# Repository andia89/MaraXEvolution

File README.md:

# MaraX Evolution - Main Controller

### Screenshot

### Videos
|  |  |
|:--:| :--:| 
| *Pressure profiling with a blind flange. The pressure follows a complicated profile* | *Real shot with the custom Controller. The profile is set to produce a flat 9bar shot that stops at 40g (since the valve is not closed by the lever there will always be some additional coffee coming out after the pump stopped). As one can see the pressure neatly follows the 9bar (at one point I adjusted with the flow control paddle so that is when the pressure dropped). The grind was way to fine for this shot :D* |

This repository contains the hardware design and firmware for the **MaraX Evolution** main controller board. This project is designed to replace the stock controller of the Lelit Mara X espresso machine, adding advanced features such as PID temperature control, pressure profiling, weighing scale integration, and WiFi connectivity.

## Features

### Core Control
* **Hybrid Thermal Control:** Utilizes a custom **Feed-Forward + PID algorithm** (`feedForwardHeater`) that estimates heat loss based on ambient vs. boiler temperature, offering better stability than standard PIDs.
* **Dual-PID Architecture:** Dedicated PID loops for Temperature (Boiler/HX) and Pump (Pressure/Flow).
* **Smart State Machine:** Manages states including `COOLING_FLUSH`, `STEAM_BOOST`, and `STANDBY`.
* Performs all tasks the original Lelit MaraX machine does as well (boiler refill, water tank presence detection, relay activations etc...)

### Profiling & Extraction
* **Pressure Profiling:** Real-time pump dimmer control via Zero-Cross detection.
* **Flow Profiling:** (Requires [MaraX Evolution Scale](https://github.com/andia89/MaraXEvolution-Scale/)) Target specific flow rates (g/s) using Kalman-filtered weight data.
* **Gravimetric stopping:** (Requires [MaraX Evolution Scale](https://github.com/andia89/MaraXEvolution-Scale/)) Stop the shot after a set amount of time or when a certain weight is reached
* **Advanced Profiles:** Supports manual control, flat 9-bar shots, or complex JSON-based profiles (Ramped or Stepped).

### Integration & Connectivity
* **WiFi & MQTT:** Full smart home integration. Reports sensors (`boiler_temp`, `pressure`, `weight`) and accepts commands remotely.
* **Telnet CLI:** Built-in command-line interface for debugging and calibration over WiFi.
* **ESP-NOW HMI:** Low-latency connection to the optional [MaraX Evolution HMI](https://github.com/andia89/maraxevolution-hmi).
* **OTA Updates:** Update firmware wirelessly without opening the machine.

### Maintenance
* **Automated Cleaning:** Built-in backflush program (`CLEANING_START` -> `CLEANING_PUMPING` -> `PAUSE`).
* **Scale Calibration:** Integrated wizard for taring and calibrating the load cell.

## Repository Structure

* `controller_board/`: KiCad v6 hardware design files (schematics, PCB layout, and fabrication files).
* `firmware/`: PlatformIO project source code for the ESP32-based controller.

## Hardware Assembly

1.  **PCB Fabrication:** Use the Gerber and Drill files provided in `controller_board/jlcpcb/production_files/` to order the PCB.
2.  **Assembly:** Solder the components according to the BOM (`BOM-controller_board.csv`). The board features an Arduino-Nano ESP32 compatible footprint. See [Assembly](ASSEMBLY.md) for details
3.  **Installation:** Replace the existing Mara X controller with this board, ensuring all connections (sensors, pump, heating element) are mapped correctly.

## Firmware Compilation

The firmware is modular. You can enable/disable hardware features via `platformio.ini` build flags:

```cpp
build_flags = 
    -D HAS_PRESSURE_GAUGE
    -D HAS_SCALE
    -D HAS_SCREEN
```

The firmware is built using **PlatformIO**.

1.  Install [VSCode](https://code.visualstudio.com/) and the [PlatformIO extension](https://platformio.org/).
2.  Clone this repository.
3.  Open the `firmware` folder in PlatformIO.
4.  Configure `platformio.ini` if necessary (e.g., to select specific build environments or upload ports)
5.  Click the **Build** icon (checkmark) to compile.
6.  Connect your Arduino Nano ESP32 board via USB and click **Upload** (select `env:firmware` build environment).
7.  For subsequent uploads OTA should be enabled (you might have to adjust IP-address in `platformio.ini`) and selecting the `env:firmware-ota` environment

## [User Guide](USERGUIDE.md)

## [Parts list](PARTS.md)

## [Assembly instructions](ASSEMBLY.md)

## Support me

I had way too much fun building the MaraX Evolution—it turned into quite the obsession! I am definitely planning to tackle another coffee machine and give it the same "Evolution" treatment.

**However, espresso machines are expensive! :D**

If you enjoy this project or use it daily, please consider supporting me.

**Your Support = Your Vote**

When you support me on Ko-fi or Patreon, **please leave a comment telling me which coffee machine you want me to do next.**

Think of it as a voting system: As soon as I have enough funds to cover the machine with the most votes (and the parts to mod it), I will buy it, reverse-engineer it, and build an open-source controller for it. If you have the MaraX and still want to support me, you can also tell me if there is a specific feature you want to have!

I will keep track of the money earned and will update occasionally the votes on the different coffee machines that are requested

## Limitations
* The MaraX is a very good heatexchanger machine, using quite sophisticated hardware to achieve superior temperature stability than a lot of other HX machines out of the box. It is, however, not a dual boiler machine and as such perfect temperature control is almost impossible. I played around a lot with PID values and was able to come up with some good values (and some pretty sophisticated feed forward control), but still perfect stability is almost impossible (or only if one tunes the PID super conservative, but then it takes hours to heat the machine)
* This is not a cheap project. Most parts can be sourced pretty cheaply, but I used good ADC chips (the ADS1115) and one unfortunately obsolete LM1830 chip for boiler water level detection as well as a pretty expensive power supply for the 12V power. Most of these things could certainly be done cheaper (and maybe someday will). All in all expect to spend a bit of money if you go for the full set (which is recommended).
* In the end the softweare got waaaaay more complicated than I originally anticipated. Some software was written using AI but I went through all of it and made sure it made sense to me. There certainly will be bugs as there is an infinite amount of edge cases I certainly have not considered. Please report any bugs you may find

## Disclaimer & Safety Warning

**PLEASE READ CAREFULLY BEFORE PROCEEDING.**

**1. I am a Hobbyist, Not a Professional**
I am **not** a professional mechanical, electrical, or software engineer. This project was created purely as a personal hobby undertaking for educational purposes. The code and hardware designs provided here are **not** certified, tested to industrial standards, or guaranteed to be bug-free.

**2. Warranty Voiding**
Modifying your espresso machine, uploading custom firmware, or opening the chassis **will almost certainly void your manufacturer’s warranty**. By proceeding with any instructions or files from this repository, you accept full responsibility for the loss of any existing warranty or support from the original manufacturer.

**3. No Liability**
This software and hardware documentation is provided **"AS IS", WITHOUT WARRANTY OF ANY KIND**, express or implied.
* **I am not responsible** for any damage to your machine (bricking the device, burning out components, leaks, etc.).
* **I am not responsible** for any personal injury or property damage (including fire or electrical shock) resulting from the use of this project.
* **You assume all risk** associated with modifying your hardware and running this software.

**4. High Voltage & Pressure Warning**
Espresso machines involve **Mains Electricity (110V/220V)**, **Water**, and **High Pressure**. This is a dangerous combination.
* Never work on the machine while it is plugged in.
* Ensure you have a proper understanding of electrical safety before attempting any hardware modifications.
* Improper handling of the boiler or pressure lines can result in explosion or severe burns.

**Use this project entirely at your own risk.**

If you find anything that you think could be improved (be it software/electrical or mechanical side) please let me know, and feel free to open a Pull request

## Licensing
This project is dual-licensed to protect the work while allowing for personal study and modification.

* **Firmware:** The main source code located in the `/firmware` directory is licensed under the **PolyForm Noncommercial License 1.0.0**. You may modify and use it for personal projects, but you cannot use it for commercial products.
    * *Third-Party Libraries:* This firmware includes modified versions of the following libraries, which remain under their original licenses:
        * [dimmable-light](https://github.com/fabianoriccardi/dimmable-light): Licensed under **LGPL-2.1**.
        * [PID_v1](https://github.com/br3ttb/Arduino-PID-Library/tree/master): Licensed under **MIT License**.
        * [Simple Kalman Filter](https://github.com/denyssene/SimpleKalmanFilter): Licensed under **MIT License**.

* **Firmware:** The hardware designs, schematics, and 3D models located in the /controller_board and /hv_board directories are licensed under the Creative Commons Attribution-NonCommercial 4.0 International (CC BY-NC 4.0) license.

Please see the LICENSE file in each respective subdirectory for the full legal text.

## Similar projects
Idea for controlling the pump via an AC dimmer has been done in https://github.com/larszi/marax-pressure-mod. A complete overhaul of control software is currently proposed by the great project in https://github.com/variegated-coffee (they try to make a one-fit all solution though)

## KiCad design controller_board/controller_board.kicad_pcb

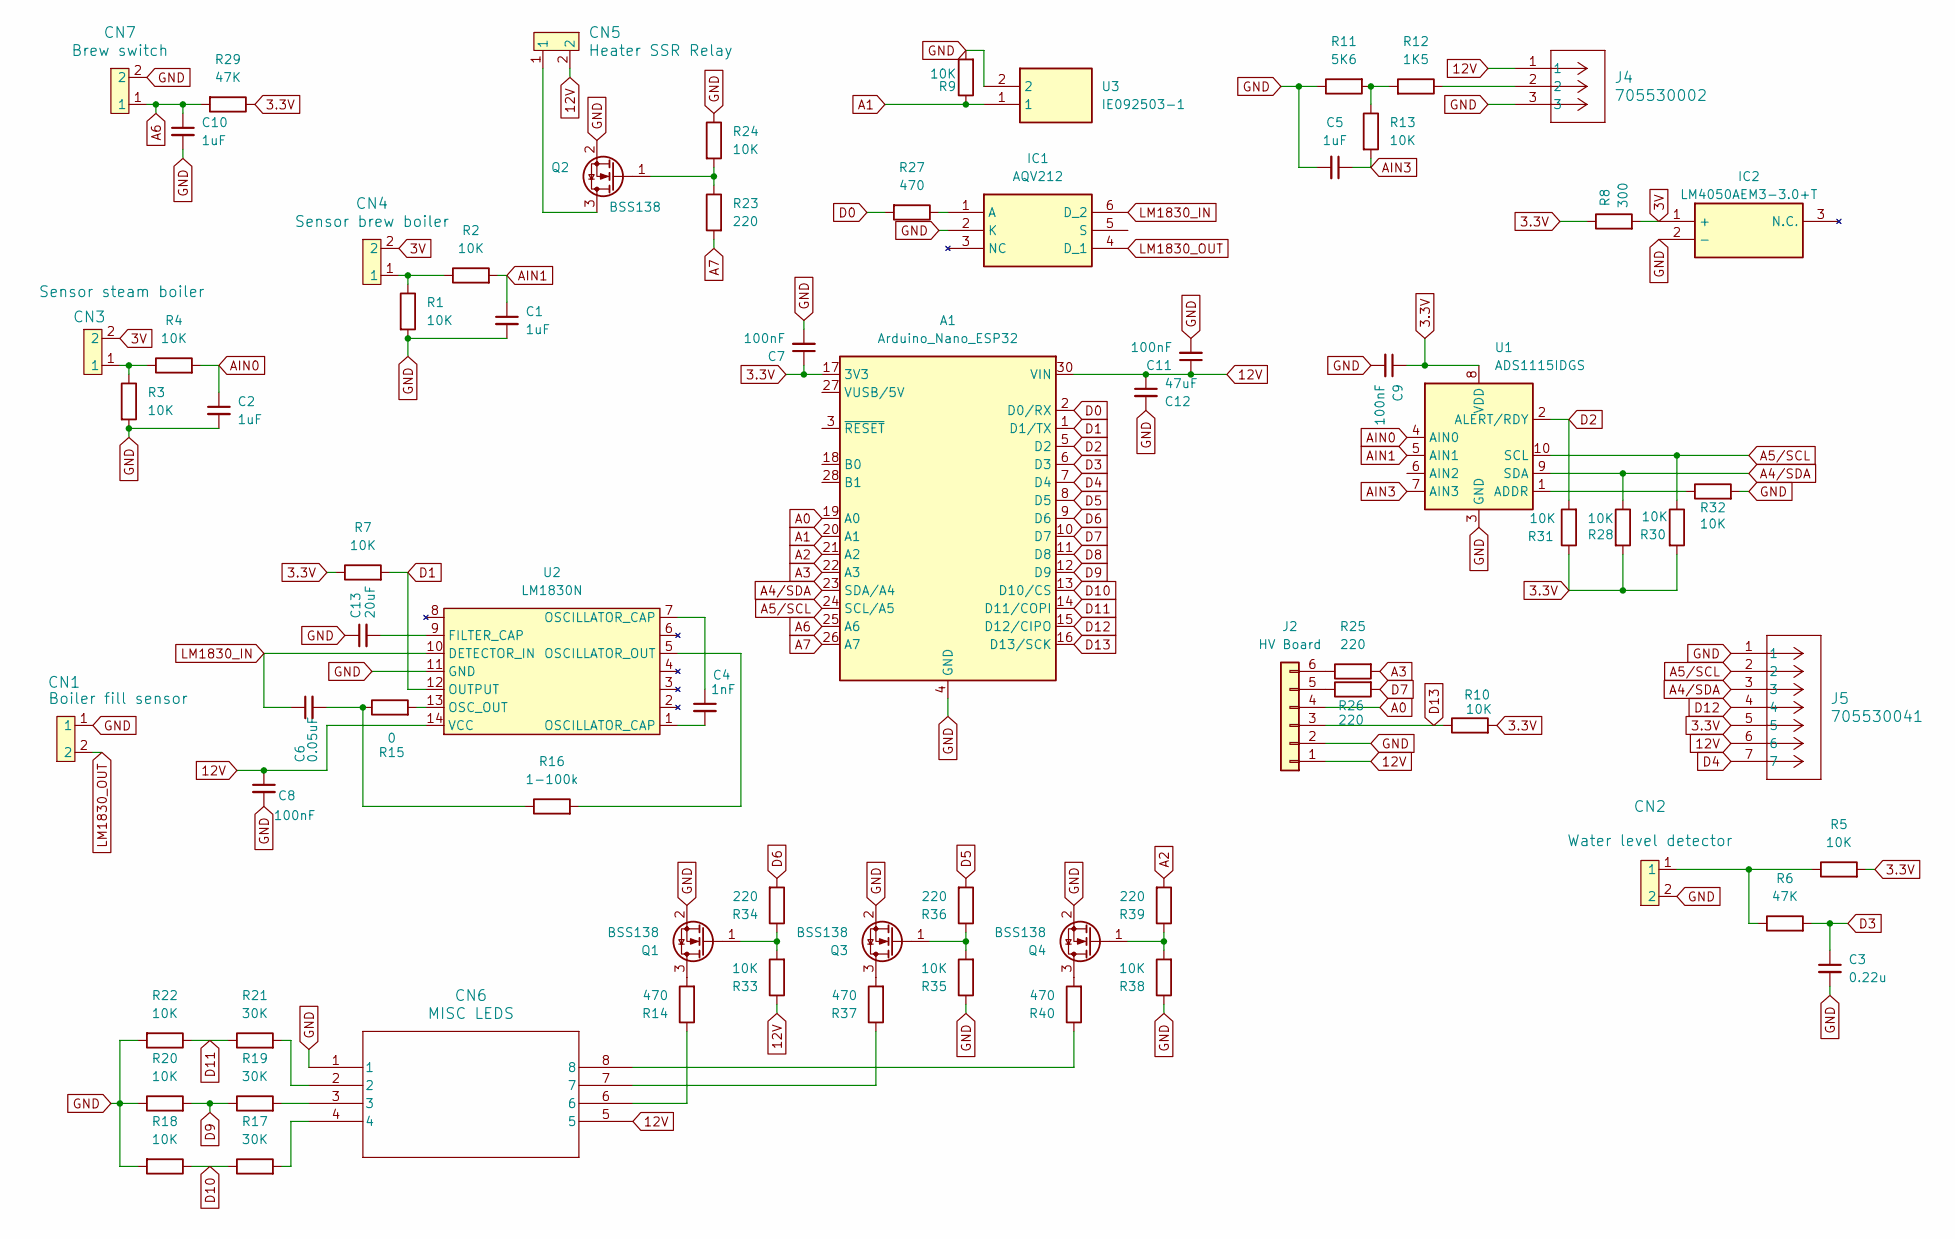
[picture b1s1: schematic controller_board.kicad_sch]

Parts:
A1: Arduino_Nano_ESP32; Arduino_Nano
C1, C2, C5, C10: 1uF; C_0805_2012Metric_Pad1.18x1.45mm_HandSolder
C3: 0.22u; C_0805_2012Metric_Pad1.18x1.45mm_HandSolder
C4: 1nF; C_0805_2012Metric_Pad1.18x1.45mm_HandSolder
C6: 0.05uF; C_0805_2012Metric_Pad1.18x1.45mm_HandSolder
C7, C8, C9, C11: 100nF; C_0805_2012Metric_Pad1.18x1.45mm_HandSolder
C12: 47uF; C_0805_2012Metric_Pad1.18x1.45mm_HandSolder
C13: 20uF; C_0805_2012Metric_Pad1.18x1.45mm_HandSolder
CN1: Boiler fill sensor; 280377-2_TYC
CN2: Water level detector; 280377-2_TYC
CN3: Sensor steam boiler; 280377-2_TYC
CN4: Sensor brew boiler; 280377-2_TYC
CN5: Heater SSR Relay; 280377-2_TYC
CN6: MISC LEDS; 280389-2_TYC
CN7: Brew switch; 280377-2_TYC
IC1: AQV212; DIP762W47P254L880H410Q6N; Mouser Part Number 769-AQV212
IC2: LM4050AEM3-3.0+T; SOT95P237X112-3N; Mouser Part Number 700-LM4050AEM3-3.0T
J2: HV Board; PinHeader_1x06_P2.00mm_Vertical
J4: 705530002; CONN_705530002_03_MOL
J5: 705530041; CONN_70553-xxxx_07_MOL
Q1, Q2, Q3, Q4: BSS138; SOT-23
R1, R2, R3, R4, R5, R7, R9, R10, R13, R18, R20, R22, R24, R28, R30, R31, R32, R33, R35, R38: 10K; R_0805_2012Metric_Pad1.20x1.40mm_HandSolder
R6, R29: 47K; R_0805_2012Metric_Pad1.20x1.40mm_HandSolder
R8: 300; R_0805_2012Metric_Pad1.20x1.40mm_HandSolder
R11: 5K6; R_0805_2012Metric_Pad1.20x1.40mm_HandSolder
R12: 1K5; R_0805_2012Metric_Pad1.20x1.40mm_HandSolder
R14, R27, R37, R40: 470; R_0805_2012Metric_Pad1.20x1.40mm_HandSolder
R15: 0; R_0805_2012Metric_Pad1.20x1.40mm_HandSolder
R16: 1-100k; R_0805_2012Metric_Pad1.20x1.40mm_HandSolder
R17, R19, R21: 30K; R_0805_2012Metric_Pad1.20x1.40mm_HandSolder
R23, R25, R26, R34, R36, R39: 220; R_0805_2012Metric_Pad1.20x1.40mm_HandSolder
U1: ADS1115IDGS; VSSOP-10_3x3mm_P0.5mm
U2: LM1830N; PDIP14_19P56X6P35_ONS
U3: IE092503-1; IE0925031; Mouser Part Number 497-IE092503-1

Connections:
3.3V: A1.17 (3V3), C7.1, C9.1, J5.5, R5.2, R7.1, R8.1, R10.2, R28.2, R29.1, R30.2, R31.1, U1.8 (VDD)
3V: CN3.2, CN4.2, IC2.1 (+), R8.2
12V: A1.30 (VIN), C8.1, C11.1, C12.1, CN5.2, CN6.5, J2.1, J4.1, J5.6, R33.1, U2.14 (VCC)
A0: A1.19 (A0), J2.4
A1: A1.20 (A1), R9.1, U3.1
A2: A1.21 (A2), R39.2
A3: A1.22 (A3), R25.2
A4/SDA: A1.23 (SDA/A4), J5.3, R28.1, U1.9 (SDA)
A5/SCL: A1.24 (SCL/A5), J5.2, R30.1, U1.10 (SCL)
A6: A1.25 (A6), C10.1, CN7.1, R29.2
A7: A1.26 (A7), R23.2
AIN0: C2.1, R4.2, U1.4 (AIN0)
AIN1: C1.1, R2.2, U1.5 (AIN1)
AIN3: C5.1, R13.2, U1.7 (AIN3)
D0: A1.2 (D0/RX), R27.2
D1: A1.1 (D1/TX), R7.2, U2.12 (OUTPUT)
D2: A1.5 (D2), R31.2, U1.2 (ALERT/RDY)
D3: A1.6 (D3), C3.1, R6.2
D4: A1.7 (D4), J5.7
D5: A1.8 (D5), R36.2
D6: A1.9 (D6), R34.2
D7: A1.10 (D7), R26.2
D8: A1.11 (D8)
D9: A1.12 (D9), R19.1, R20.2
D10: A1.13 (D10/CS), R17.1, R18.1
D11: A1.14 (D11/COPI), R21.1, R22.1
D12: A1.15 (D12/CIPO), J5.4
D13: A1.16 (D13/SCK), J2.3, R10.1
GND: A1.4 (GND), A1.29 (GND), C1.2, C2.2, C3.2, C5.2, C7.2, C8.2, C9.2, C10.2, C11.2, C12.2, C13.1, CN1.1, CN2.2, CN6.1, CN7.2, IC1.2 (K), IC2.2 (-), J2.2, J4.3, J5.1, Q1.2 (S), Q2.2 (S), Q3.2 (S), Q4.2 (S), R1.2, R3.2, R9.2, R11.1, R18.2, R20.1, R22.2, R24.1, R32.2, R35.1, R38.1, U1.3 (GND), U2.11 (GND), U3.2
LM1830_IN: C6.1, IC1.6 (D_2), U2.10 (DETECTOR_IN)
LM1830_OUT: CN1.2, IC1.4 (D_1)
unnamed: C4.1, U2.7 (OSCILLATOR_CAP)
unnamed: C4.2, U2.1 (OSCILLATOR_CAP)
unnamed: C6.2, R15.1, R16.1
unnamed: CN2.1, R5.1, R6.1
unnamed: CN3.1, R3.1, R4.1
unnamed: CN4.1, R1.1, R2.1
unnamed: CN6.2, R21.2
unnamed: CN6.3, R19.2
unnamed: CN6.4, R17.2
unnamed: CN6.6, R14.1
unnamed: CN6.7, R37.1
unnamed: CN6.8, R40.1
unnamed: IC1.1 (A), R27.1
unnamed: J2.5, R26.1
unnamed: J2.6, R25.1
unnamed: J4.2, R12.1
unnamed: Q1.3 (D), R14.2
unnamed: Q1.1 (G), R33.2, R34.1
unnamed: CN5.1, Q2.3 (D)
unnamed: Q2.1 (G), R23.1, R24.2
unnamed: Q3.3 (D), R37.2
unnamed: Q3.1 (G), R35.2, R36.1
unnamed: Q4.3 (D), R40.2
unnamed: Q4.1 (G), R38.2, R39.1
unnamed: R11.2, R12.2, R13.1
unnamed: R32.1, U1.1 (ADDR)
unnamed: C13.2, U2.9 (FILTER_CAP)
unnamed: R16.2, U2.5 (OSCILLATOR_OUT)
unnamed: R15.2, U2.13 (OSC_OUT)

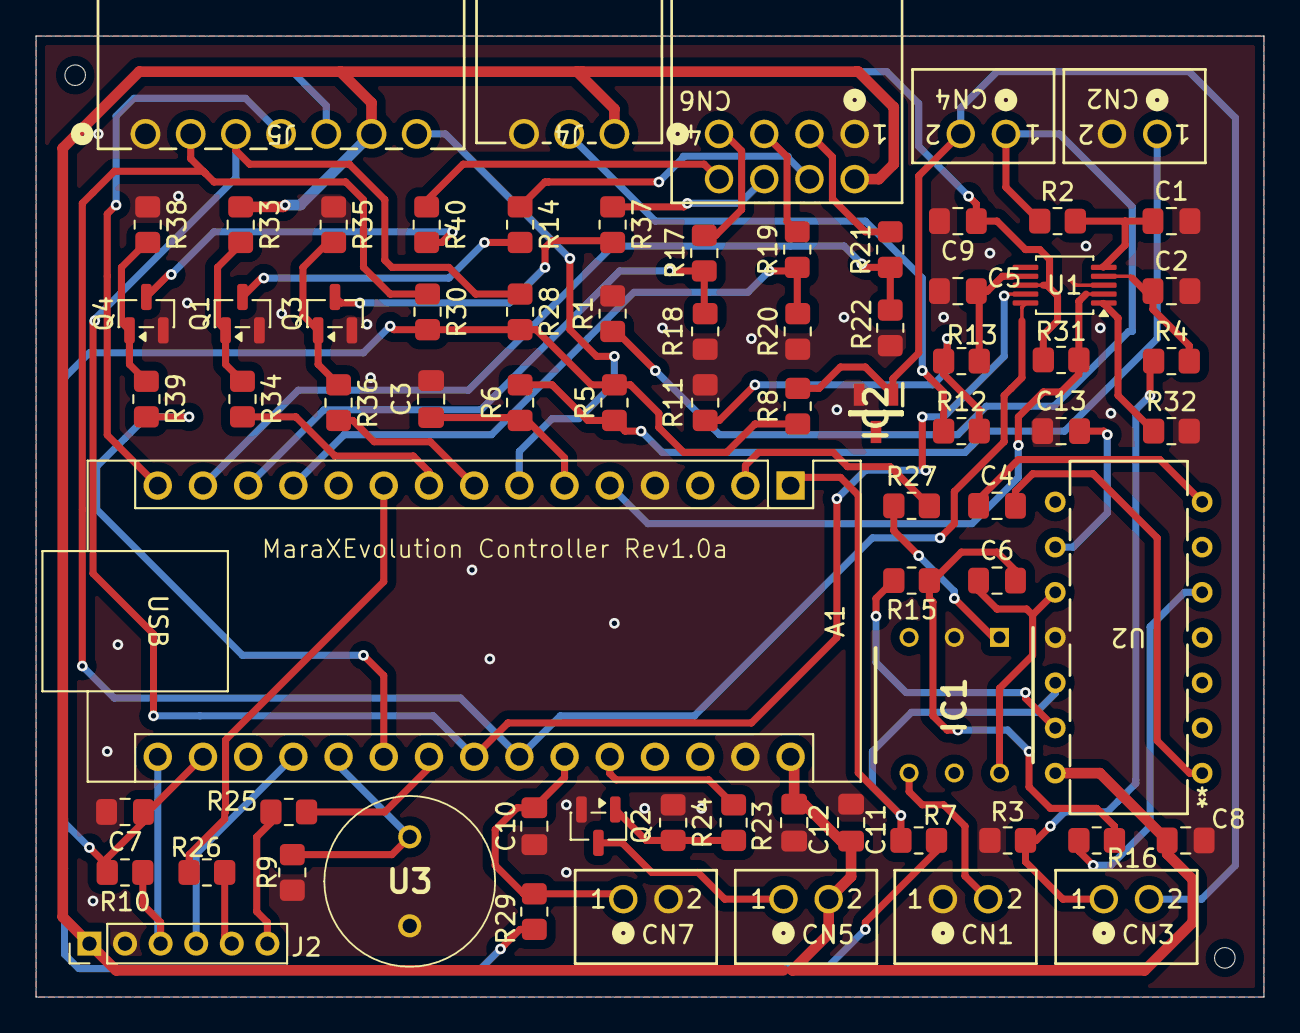
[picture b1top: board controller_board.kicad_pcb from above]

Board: 2 copper layers, 69.0 x 54.0 mm, 73 parts (0 on the bottom side), 59 nets.

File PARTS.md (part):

## Parts List

 * PCBs for both the controller board and the HV board. I had good experience with JLCPCB but PCBWay is also fine. The gerber files can be found in production_files in the jlcpcb folder. 

* Electronic parts for assembly. They are listed at the end of this section in [Controller board](#conroller-board) and [HV board](#hv-board)

* If you want to use a pressure transducer (this is necessary to do profiling based on pressure, and to electronically monitor the pressure). 
    * The board is designed for [this one](https://aliexpress.com/item/4000756631924.html?spm=a2g0o.ord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; specifically 0-1.6MPa at 0.5V-4.5V and a supply voltage of 12V
    * [T-Piece for pipe](https://www.landefeld.de/artikel/de/t-steckanschluss-5mm-5mm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 It is important to note that the MaraX uses 5mm pipes which are quite non-standard
    * [Pipe push fitting](https://www.landefeld.de/artikel/de/steckanschluss-m-innenge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
    * [5mm polyurethane pipe](https://www.landefeld.de/artikel/de/polyurethan-schlauch-5-x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; get 1m to have a bit left-over
    * [Molex connector](https://www.mouser.at/ProductDetail/Molex/50-57-9403?qs=u6Gr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 that has its mate on the controller board, with at least [3 Receptables that need to be crimped on the wire](https://www.mouser.at/ProductDetail/Molex/16-02-0102?qs=UAyr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
* If you want to use AC dimmer for flow/pressure profiling (and you either have the Pressure transducer and/or the scale installed) one additional (ideally heat-resistant cable) is necessary. Two [Connectors](https://www.mouser.at/ProductDetail/571-606501) like this one have to be crimped on a sufficiently long cable. 

### Controller Board

The BOM for the controller board is divided into **SMD components** (suitable for JLCPCB's SMT service) and **Handsolder components** (precision parts, connectors, and the microcontroller to be sourced from Mouser/DigiKey).

#### 1. SMD Components (JLCPCB SMT Service)
These components have LCSC part numbers included in the BOM and can be assembled by the JLCPCB SMT service. Alternatively they can be of course hand soldered. These Resistors and Capacitors are mainly used for Pull-up/down, current limiting and filtering, as such their exact values are not that important. The transistors are mainly used for switching LEDs. In both controller_board and hv_board folder there is a jlcpcb folder that contains all the necessary files for fabrication as well as SMT assembly.

| Comment | Designator | Footprint | LCSC Part | Qty |
| :--- | :--- | :--- | :--- | :--- |
| **0** | R15 | R 0805 | [C17477](https://lcsc.com/product-detail/C17477.html) | 1 |
| **0.05uF** | C6 | C 0805 | [C53134](https://lcsc.com/product-detail/C53134.html) | 1 |
| **0.22u** | C3 | C 0805 | [C5378](https://lcsc.com/product-detail/C5378.html) | 1 |
| **100nF** | C7, C8, C9, C11 | C 0805 | [C28233](https://lcsc.com/product-detail/C28233.html) | 4 |
| **1nF** | C4 | C 0805 | [C46653](https://lcsc.com/product-detail/C46653.html) | 1 |
| **1uF** | C1, C2, C5, C10 | C 0805 | [C28323](https://lcsc.com/product-detail/C28323.html) | 4 |
| **10K** | R1, R3, R5, R7, R9, R10, **R13**, R18, R20, R22, R24, R28, R30, R31, R32, R33, R35, R38 | R 0805 | [C17414](https://lcsc.com/product-detail/C17414.html) | 18 |
| **20uF** | C13 | C 0805 | [C45783](https://lcsc.com/product-detail/C45783.html) | 1 |
| **47uF** | C12 | C 0805 | [C28323](https://lcsc.com/product-detail/C28323.html) | 1 |
| **220** | R23, R25, R26, R34, R36, R39 | R 0805 | [C17557](https://lcsc.com/product-detail/C17557.html) | 6 |
| **300** | R8 | R 0805 | [C17617](https://lcsc.com/product-detail/C17617.html) | 1 |
| **30K** | R17, R19, R21 | R 0805 | [C17621](https://lcsc.com/product-detail/C17621.html) | 3 |
| **470** | R14, R27, R37, R40 | R 0805 | [C17710](https://lcsc.com/product-detail/C17710.html) | 4 |
| **47K** | R6, R29 | R 0805 | [C17713](https://lcsc.com/product-detail/C17713.html) | 2 |
| **BSS138** | Q1, Q2, Q3, Q4, Q5, Q6 | SOT-23 | [C15277](https://lcsc.com/product-detail/C15277.html) | 6 |

#### 2. Handsolder Components (Mouser / DigiKey)
These parts are not included in the SMT assembly and must be purchased separately.

**Precision Resistors**
*0.1% tolerance is recommended for these voltage dividers. If this is really necessary I am not sure, but I used 0.1% tolerance ones and it works great*

| Value | Designator | Qty | Link (Mouser) |
| :--- | :--- | :--- | :--- |
| **1K5** | R12 | 1 | [0805 1.5K 0.1%](https://www.mouser.com/c/?q=0805%20resistor%201.5kOhms%200.1%25) |
| **5K6** | R11 | 1 | [0805 5.6K 0.1%](https://www.mouser.com/c/?q=0805%20resistor%205.6kOhms%200.1%25) |
| **10K** | R2, R4 | 2 | [0805 10K 0.1%](https://www.mouser.com/c/?q=0805%20resistor%2010kOhms%200.1%25) |
| **-** | **R16** | **0** | **DNP (Do Not Populate)** |

**ICs & Modules**

| Part Name | Designator | Description | Qty | Link (Mouser) | Comment | 
| :--- | :--- | :--- | :--- | :--- | :--- |
| **Arduino Nano ESP32**| A1 | Microcontroller | 1 | [Arduino Nano ESP32](https://www.mouser.com/c/?q=Arduino%20Nano%20ESP32) | with headers if directly soldered to the board. Otherwise [Mill-Max](https://www.mill-max.com/products/new/precision-machined-pin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 headers are a way to socket it (there is not enough vertical space for standard machine headers)
| **ADS1115IDGS** | U1 | 16-Bit ADC | 1 | [ADS1115IDGS](https://www.mouser.com/c/?q=ADS1115IDGS) | Any ADS1115 will work fine
| **AQV212** | IC1 | PhotoMOS Relay | 1 | [AQV212](https://www.mouser.com/c/?q=AQV212%20DIP-6) | can be socketed using standard DIP-6 socket
| **IE092503-1** | U3 | Buzzer | 1 | [IE092503-1](https://www.mouser.com/c/?q=IE092503-1) | If you don't want a buzzer, can be omitted
| **LM4050AEM3-3.0** | IC2 | Voltage Reference 3.0V | 1 | [LM4050AEM3-3.0](https://www.mouser.com/c/?q=LM4050AEM3-3.0) | A precise voltage reference for temperature measurements

**Connectors**

| Part Name | Designator | Description | Qty | Link (Mouser) | Comment | 
| :--- | :--- | :--- | :--- | :--- | :--- |
| **280377-2** | CN1, CN2, CN3, CN4, CN5, CN7 | TE Ampmodu II (2 pos) | 6 | [TE 280377-2](https://www.mouser.com/c/?q=280377-2) |
| **280389-2** | CN6 | TE Ampmodu II (8 pos) | 1 | [TE 280389-2](https://www.mouser.com/c/?q=280389-2) |
| **70553-0002** | J4 | Molex SL Header (3 pos)| 1 | [Molex 70553-0002](https://www.mouser.com/c/?q=705530002) | Can be omitted if no pressure transducer is to be installed
| **70553-0041** | J5 | Molex SL Header (7 pos) | 1 | [Molex 70553-0041](https://www.mouser.com/c/?q=705530041) | Can be omitted if no scale is to be installed
| **MTMM-106-14-T-S-520** | J2 | 2.00mm Pitch Header | 1 | [Header 1x06 2mm](https://www.mouser.com/c/?q=MTMM-106-14-T-S-520) | This mates with the correspnding ESQT connector on the HV board. The exact part numbers are not that important, but the two connectors need to bridge a gap of 27mm (distance between the topsides of both PCBs)

#### 3. Special Components
This component is obsolete and typically requires sourcing from eBay.

| Component | Designator | Note | Link | Comment |
| :--- | :--- | :--- | :--- | :--- |
| **LM1830N** | U2 | Fluid Level Detector | [Search on eBay](https://www.ebay.com/sch/i.html?_nkw=LM1830N) | Can be socketed by using socket for N14A package

### HV Board

These components have LCSC part numbers included in the BOM and can be assembled by the JLCPCB SMT service. Alternatively they can be of course hand soldered. These Resistors and Capacitors are mainly used for Pull-up/down, current limiting and filtering, as such their exact values are not that important. Transistors are used to switch the Relays and Diodes as flyback. Both can be cheaply done with SMT service from JLCPCB

#### 1. SMD Components (JLCPCB SMT Service)
These components have LCSC part numbers and can be assembled by the JLCPCB SMT service.

| Comment | Designator | Footprint | LCSC Part | Qty |
| :--- | :--- | :--- | :--- | :--- |
| **100** | R8 | R 0805 | [C17408](https://lcsc.com/product-detail/C17408.html) | 1 |
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
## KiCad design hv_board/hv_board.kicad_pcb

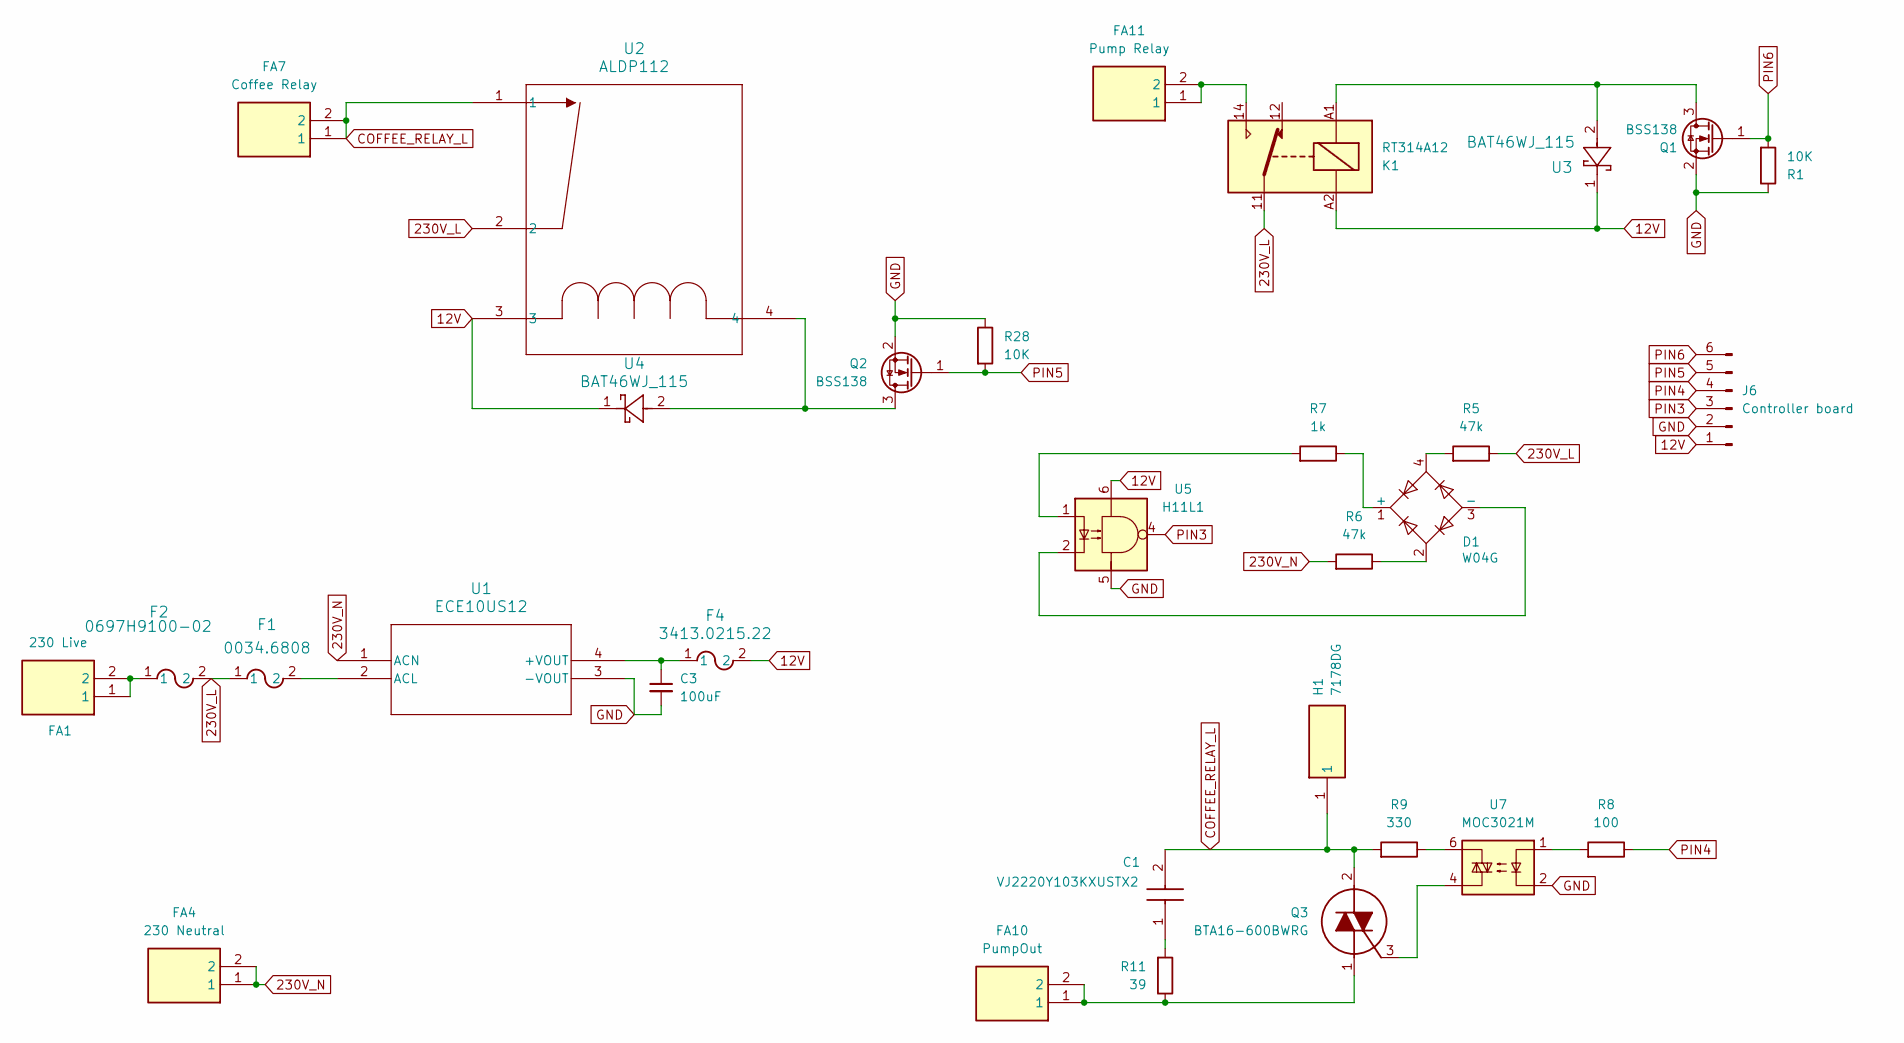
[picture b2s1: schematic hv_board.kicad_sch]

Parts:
C1: VJ2220Y103KXUSTX2; CAPC5651X218N; Mouser Part Number 77-VJ2220Y103KXUSTX2
C3: 100uF; CP_Radial_D6.3mm_P2.50mm
D1: W04G; Diode_Bridge_Round_D9.8mm
F1: 0034.6808; FUS_SCHURTER_0034_SCH
F2: 0697H9100-02; 0697_BEL
F4: 3413.0215.22; FUS1206_24N_SCH
FA1: 230 Live; 1606502; Manufacturer_Part_Number 160650-2; Mouser Part Number 571-160650-2
FA4: 230 Neutral; 1606502; Manufacturer_Part_Number 160650-2; Mouser Part Number 571-160650-2
FA7: Coffee Relay; 1606502; Manufacturer_Part_Number 160650-2; Mouser Part Number 571-160650-2
FA10: PumpOut; 1606502; Manufacturer_Part_Number 160650-2; Mouser Part Number 571-160650-2
FA11: Pump Relay; 1606502; Manufacturer_Part_Number 160650-2; Mouser Part Number 571-160650-2
H1: 7178DG; Mouser Part Number 532-7178DG
J6: Controller board; PinHeader_1x06_P2.00mm_Vertical
K1: RT314A12; Relay_SPDT_Schrack-RT1-16A-FormC_RM5mm
Q1, Q2: BSS138; SOT-23
Q3: BTA16-600BWRG; TO255P460X1020X2005-3P; Mouser Part Number 511-BTA16-600BW
R1, R28: 10K; R_0805_2012Metric_Pad1.20x1.40mm_HandSolder
R5, R6: 47k; R_2010_5025Metric_Pad1.40x2.65mm_HandSolder
R7: 1k; R_0805_2012Metric_Pad1.20x1.40mm_HandSolder
R8: 100; R_0805_2012Metric_Pad1.20x1.40mm_HandSolder
R9: 330; R_2010_5025Metric_Pad1.40x2.65mm_HandSolder
R11: 39; R_2010_5025Metric_Pad1.40x2.65mm_HandSolder
U1: ECE10US12; RELAY4_ECE10_XPR
U2: ALDP112; PAN_ALD_PAN
U3, U4: BAT46WJ_115; SC-90_SOD323F_NEX
U5: H11L1; H11L1_ISO
U7: MOC3021M; PDIP6_BX_ONS

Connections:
12V: F4.2, J6.1, K1.A2, U2.3, U3.1, U4.1, U5.6
230V_L: F1.1, F2.2, K1.11, R5.1, U2.2
230V_N: FA4.1, FA4.2, R6.2, U1.1 (ACN)
COFFEE_RELAY_L: C1.2, FA7.1, FA7.2, H1.1, Q3.2 (A2), R9.2, U2.1
GND: C3.2, J6.2, Q1.2 (S), Q2.2 (S), R1.1, R28.1, U1.3 (-VOUT), U5.5, U7.2
unnamed: C1.1, R11.2
unnamed: D1.1 (+), R7.1
unnamed: D1.3 (-), U5.2
unnamed: D1.2, R6.1
unnamed: D1.4, R5.2
unnamed: F2.1, FA1.1, FA1.2
unnamed: FA11.1, FA11.2, K1.14
unnamed: K1.A1, Q1.3 (D), U3.2
unnamed: Q2.3 (D), U2.4, U4.2
unnamed: FA10.1, FA10.2, Q3.1 (A1), R11.1
unnamed: Q3.3 (G), U7.4
unnamed: R7.2, U5.1
unnamed: R8.2, U7.1
unnamed: R9.1, U7.6
unnamed: C3.1, F4.1, U1.4 (+VOUT)
unnamed: F1.2, U1.2 (ACL)
PIN3: J6.3, U5.4
PIN4: J6.4, R8.1
PIN5: J6.5, Q2.1 (G), R28.2
PIN6: J6.6, Q1.1 (G), R1.2

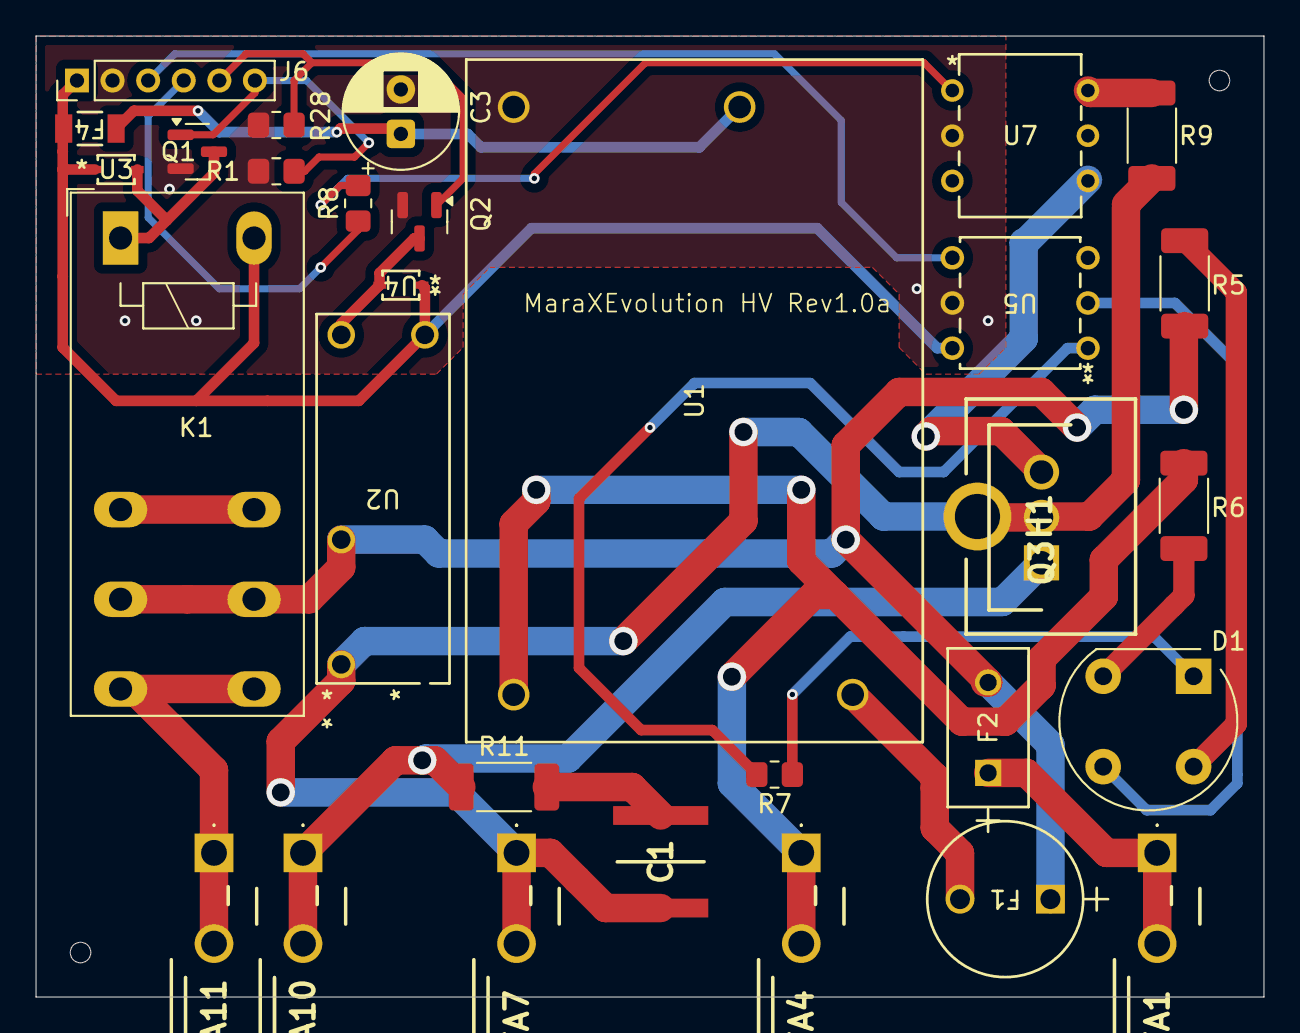
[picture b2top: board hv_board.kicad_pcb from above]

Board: 2 copper layers, 69.0 x 54.0 mm, 31 parts (0 on the bottom side), 25 nets.

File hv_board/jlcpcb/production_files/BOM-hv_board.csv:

Comment,Designator,Footprint,LCSC,Quantity
100,R8,R_0805_2012Metric_Pad1.20x1.40mm_HandSolder,C17408,1
10K,"R1,R28",R_0805_2012Metric_Pad1.20x1.40mm_HandSolder,C17414,2
1k,R7,R_0805_2012Metric_Pad1.20x1.40mm_HandSolder,C17513,1
BAT46WJ_115,"U3,U4",SC-90_SOD323F_NEX,C7502692,2
BSS138,"Q1,Q2",SOT-23,C7420339,2
ALDP112,U2,PAN_ALD_PAN,,1
H11L1,U5,H11L1_ISO,,1
47k,R6,R_2010_5025Metric_Pad1.40x2.65mm_HandSolder,,1
0034.6808,F1,FUS_SCHURTER_0034_SCH,,1
W04G,D1,Diode_Bridge_Round_D9.8mm,,1
47k,R5,R_2010_5025Metric_Pad1.40x2.65mm_HandSolder,,1
7178DG,H1,7178DG,,1
MOC3021M,U7,PDIP6_BX_ONS,,1
230 Live,FA1,1606502,,1
VJ2220Y103KXUSTX2,C1,CAPC5651X218N,,1
Pump Relay,FA11,1606502,,1
39,R11,R_2010_5025Metric_Pad1.40x2.65mm_HandSolder,,1
RT314A12,K1,Relay_SPDT_Schrack-RT1-16A-FormC_RM5mm,,1
3413.0215.22,F4,FUS1206_24N_SCH,,1
230 Neutral,FA4,1606502,,1
BTA16-600BWRG,Q3,TO255P460X1020X2005-3P,,1
PumpOut,FA10,1606502,,1
100uF,C3,CP_Radial_D6.3mm_P2.50mm,,1
330,R9,R_2010_5025Metric_Pad1.40x2.65mm_HandSolder,,1
Coffee Relay,FA7,1606502,,1
ECE10US12,U1,RELAY4_ECE10_XPR,,1
0697H9100-02,F2,0697_BEL,,1
Controller board,J6,PinHeader_1x06_P2.00mm_Vertical,,1

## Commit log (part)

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2025-12-25 Adds gitignore
2025-12-25 Add LICENSE.md for Creative Commons license
    Added the Creative Commons Attribution-NonCommercial-NoDerivatives 4.0 International Public License to the project.
2025-12-25 Add LICENSE file with CC BY-NC-ND 4.0 License
    Added Creative Commons Attribution-NonCommercial-NoDerivatives 4.0 International Public License to the project.
2025-12-25 Add PolyForm Noncommercial License 1.0.0
    This file outlines the terms of the PolyForm Noncommercial License 1.0.0, including acceptance, copyright, distribution, and usage rights.
2025-12-25 Add licensing section to README
    Added licensing information for firmware and hardware.
2025-12-25 Add disclaimer and safety warning to README
    Added a disclaimer and safety warning section to the README.
2025-12-25 Add upgrade options section to README
    Added options for upgrades section to README.
2025-12-25 Improve licensing section formatting in README
    Updated licensing section for clarity and formatting.
2025-12-25 Revise README for MaraX Evolution project
    Updated README to provide detailed project information, features, repository structure, assembly instructions, firmware compilation steps, and dependencies for the MaraX Evolution main controller.
2025-12-27 Add parts list and component details to README
    Added a parts list section with details on components and recommendations for resistor tolerances.
2025-12-27 New bom
2025-12-30 New gerber files
2025-12-30 Adds parts list for controller board to README
2025-12-30 updated parts list
2025-12-30 Adds part list for HV board
2026-01-03 allow cleaning when in heating and warm enough
2026-01-03 check for hx temp not boiler temp for cleaning requirement
2026-01-03 updates to README
2026-01-10 newparts list
2026-01-26 Many fixes
2026-01-28 Adds better support for offline machine
2026-02-02 Better handling of offline state
2026-02-02 markdown changes
2026-02-02 Enhance assembly instructions with images
    Added multiple images to assembly instructions.
2026-02-02 Added initial draft for text
2026-02-02 Update ASSEMBLY.md with assembly instructions and images
    Added detailed assembly instructions and images for the controller and HV boards, including key assembly notes and wiring connections.
2026-02-02 Add images to README for MaraX Evolution
    Added images to README for visual representation.
2026-02-02 Remove redundant image link from README
    Removed an image link from the README file.
2026-02-02 Enhance README with limitations and similar projects
    Added limitations and similar projects sections to README.
2026-02-02 Update cost details in README limitations section
    Clarified project cost details in limitations section.
2026-02-02 Revise USERGUIDE for MaraX Evolution updates
    Updated user manual to reflect changes for MaraX Evolution, including machine states, MQTT topics, and HomeAssistant integration details.
2026-02-02 Revise README features and assembly instructions
    Updated feature descriptions for clarity and added details about optional upgrades and integration.
2026-02-02 Expand README with core control and profiling details
    Added detailed sections on core control, profiling, integration, and maintenance features.
2026-02-02 Add link to MaraX Evolution Scale in README
    Updated README to include link to MaraX Evolution Scale for flow profiling.
2026-02-02 Adds telnet exit logic
2026-02-03 Use platform.io build flags
2026-02-04 Encourage support and outline future project plans
    Added a section encouraging support for future projects and explaining the voting system for the next coffee machine build.
2026-02-04 Add Ko-fi username to FUNDING.yml
    Added Ko-fi username for funding support.
2026-02-04 Modify funding information in FUNDING.yml
    Updated GitHub Sponsors and Ko-fi usernames.
2026-02-04 Update README to include funding and voting information
    Added a note about tracking funds and votes for coffee machines.
2026-02-04 Add image link to README
    Added an additional image link to the README file.
2026-02-04 Update README with additional Lelit MaraX features
    Added functionality details for Lelit MaraX machine.
2026-02-04 Adds support for gravimetric stopping
2026-02-05 Update README with gravimetric stopping feature
    Added gravimetric stopping feature details to README.
2026-02-06 Modify image tags in README.md
    Updated image links in README to adjust sizes.
2026-02-06 Add screenshot and video sections to README
2026-02-06 Revise videos section layout in README
    Updated the videos section to display images in a table format with descriptions.
2026-02-06 Fix formatting in README.md for video descriptions
2026-02-06 Fix formatting in README.md video descriptions
2026-02-06 Fix description of real shot with custom Controller
    Updated the description of the real shot with the custom Controller to reflect the correct weight and behavior of the valve.
2026-02-08 Set pump power to 100 for flushing and cleaning
2026-02-13 Prevent erroneous shutdown if scale reads negative values
2026-02-13 We go to heating after brewing
2026-02-13 Revert "We go to heating after brewing"
    This reverts commit a1cfc95fdf79d9c06c25716c0c21d30a51324217.
2026-02-14 Tare scale on startup
2026-02-14 No cooling flush immediately after brewing
2026-02-14 Wait a bit when entering heating state to go to idle
2026-02-15 Let the controller handle the profile array and reduce flash wear when saving
2026-02-16 Fixes for profile
2026-02-24 Better handling of blooming
2026-03-26 We don't cancel the shot when water is empty during brew
2026-05-11 the callback should do as little as possible. prevents out of memory errors in espnow

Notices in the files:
README.md:
License: PolyForm Noncommercial
